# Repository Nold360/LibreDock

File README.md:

# LibreDock

LibreDock is a MAX4885-based VGA Docking PCB for portable devices. It allows switching VGA and up to four controller signal lines using a very small PCB.

As a docking connector it uses HDMI, which is "misused" for this purpose.

## Features & Requirements

Switching of:
  - VGA (R,G,B,H & V)
  - Player 1 Controller Data (Controller 2, 3 and 4 are only available in "docked mode")

Additional Features:
  - Charging through dock
  - Stereo Audio (L & R) to dock

Requirements:
  - 5v & 3.3v

## Front

## Back

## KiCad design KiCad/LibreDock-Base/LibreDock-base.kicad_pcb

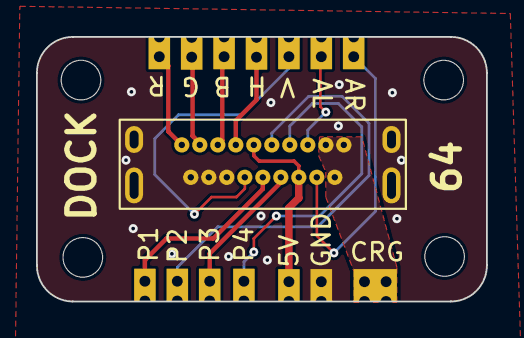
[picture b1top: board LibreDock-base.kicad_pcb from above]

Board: 2 copper layers, 25.0 x 14.7 mm, 19 parts (0 on the bottom side), 14 nets.

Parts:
H1, H2, H3, H4: MountingHole; MountingHole_2.2mm_M2
J1: SS-53000-001; HDMI Male Type-A Elecbee
R1: G; CasPowerPad 2x1
R2: B; CasPowerPad 2x1
R3: H; CasPowerPad 2x1
R4: V; CasPowerPad 2x1
R5: P1; CasPowerPad 2x1
R6: P2; CasPowerPad 2x1
R7: P3; CasPowerPad 2x1
R8: P4; CasPowerPad 2x1
R9: AL; CasPowerPad 2x1
R10: AR; CasPowerPad 2x1
R11: GND; CasPowerPad 2x1
R12: 5V; CasPowerPad 2x1
R13: R; CasPowerPad 2x1
U1: CRG; CasPowerPad 2x2

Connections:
5v: J1.9, J1.14, R12.1
AL: J1.15, R9.1
AR: J1.16, R10.1
B: J1.5, R2.1
C1: J1.10, R5.1
C2: J1.11, R6.1
C3: J1.12, R7.1
C4: J1.13, R8.1
CHARGE: J1.17, J1.18, J1.19, U1.1 (Vout)
G: J1.3, R1.1
GND: J1.2, J1.4, J1.6, J1.S1 (SHIELD), J1.S2 (SHIELD), J1.S3 (SHIELD), J1.S4 (SHIELD), R11.1
H: J1.7, R3.1
R: J1.1, R13.1
V: J1.8, R4.1

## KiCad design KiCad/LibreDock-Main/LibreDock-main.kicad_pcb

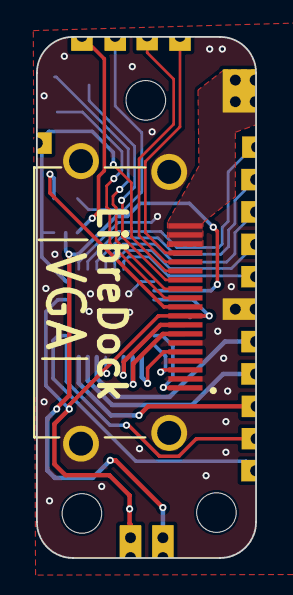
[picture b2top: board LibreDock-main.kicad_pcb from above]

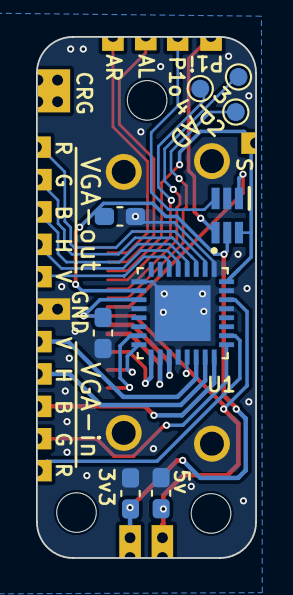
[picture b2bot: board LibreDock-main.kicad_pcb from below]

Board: 2 copper layers, 12.2 x 29.0 mm, 32 parts (24 on the bottom side), 28 nets.

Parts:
C1, C2, C3, C4: C_Small; C_0603_1608Metric_Pad1.08x0.95mm_HandSolder
H1, H2, H3: MountingHole; MountingHole_2.2mm_M2
IC1: PI5A3157CEX; SOT65P210X110-6N
J1: SS-53000-001; STEWART_SS-53000-001
TP1, TP6: B; CasPowerPad 1x1
TP2, TP7: G; CasPowerPad 1x1
TP3, TP8: R; CasPowerPad 1x1
TP4, TP9: H; CasPowerPad 1x1
TP5, TP10: V; CasPowerPad 1x1
TP11: P1i; CasPowerPad 1x1
TP12: P1o; CasPowerPad 1x1
TP13: 5v; CasPowerPad 2x1
TP14: 3v3; CasPowerPad 2x1
TP15: GND; CasPowerPad 2x1
TP16: AL; CasPowerPad 1x1
TP17: AR; CasPowerPad 1x1
TP18: S; CasPowerPad 1x1
TP19: P2; nolds-TestPoint_Pad_D1.0mm
TP20: P3; nolds-TestPoint_Pad_D1.0mm
TP21: P4; nolds-TestPoint_Pad_D1.0mm
TP22: CRG; CasPowerPad 2x2
U1: MAX4885ETJ_; QFN50P500X500X80-33N

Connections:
3v3: C1.1, C2.1, IC1.5 (VCC), TP14.1, U1.10 (VCL)
5v: C3.2, C4.2, J1.9, TP13.1, U1.11 (V+), U1.21 (V+), U1.30 (V+)
AL: J1.15, TP16.1
AR: J1.16, TP17.1
B: J1.5, U1.17 (B2)
C1: IC1.1 (B1), J1.10
C2: J1.11, TP19.1
C3: J1.12, TP20.1
C4: J1.13, TP21.1
CHARGE: J1.17, J1.18, J1.19, TP22.1
G: J1.3, U1.16 (G2)
GND: C1.2, C2.2, C3.1, C4.1, IC1.2 (GND), J1.2, J1.4, J1.6, J1.S1 (SHIELD), J1.S2 (SHIELD), J1.S3 (SHIELD), J1.S4 (SHIELD), TP15.1, U1.1 (~QP), U1.9 (~EN), U1.12 (GND), U1.20 (GND), U1.29 (GND), U1.31 (M), U1.33 (EP)
H: J1.7, U1.18 (H2)
unnamed: IC1.4 (A), TP11.1
unnamed: IC1.3 (B0), TP12.1
unnamed: TP1.1, U1.4 (B0)
unnamed: TP6.1, U1.24 (B1)
unnamed: TP2.1, U1.3 (G0)
unnamed: TP7.1, U1.25 (G1)
unnamed: TP4.1, U1.5 (H0)
unnamed: TP9.1, U1.23 (H1)
unnamed: TP3.1, U1.2 (R0)
unnamed: TP8.1, U1.26 (R1)
unnamed: TP5.1, U1.6 (V0)
unnamed: TP10.1, U1.22 (V1)
R: J1.1, U1.15 (R2)
SENSE: IC1.6 (S), J1.14, TP18.1, U1.32 (SEL)
V: J1.8, U1.19 (V2)

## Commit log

2024-12-28 init
